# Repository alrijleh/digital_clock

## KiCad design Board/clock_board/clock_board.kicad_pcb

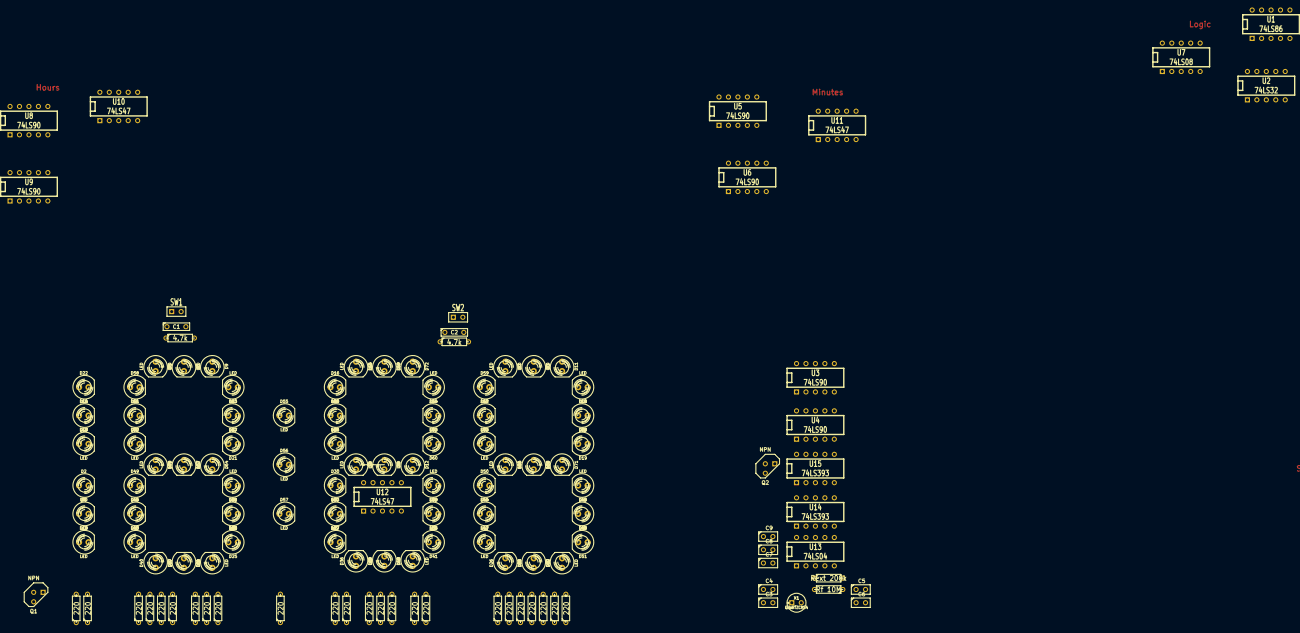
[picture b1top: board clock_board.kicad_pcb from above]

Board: 2 copper layers, 129 parts (0 on the bottom side), 74 nets, no tracks yet.

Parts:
C1, C2: .5uF; C2
C3: C1 15pF; C1
C4: C1 25pF; C1
C5: C2 25pF; C1
C6: C2 0pF; C1
C7, C8: Co 25pF; C1
C9: Co 0pF; C1
D1, D2, D3, D4, D5, D6, D7, D8, D9, D10, D11, D12, D13, D14, D15, D16, D17, D18, D19, D20, D21, D22, D23, D24, D25, D26, D27, D28, D29, D30, D31, D32, D33, D34, D35, D36, D37, D38, D39, D40, D41, D42, D43, D44, D45, D46, D47, D48, D49, D50, D51, D52, D53, D54, D55, D56, D57, D58, D59, D60, D61, D62, D63, D64, D65, D66, D67, D68, D69, D70, D71, D72: LED; LED-5MM
Q1, Q2: NPN; TO92
R1, R13: 4.7k; R3
R2, R3, R4, R5, R6, R7, R8, R9, R10, R11, R12, R14, R15, R16, R17, R18, R19, R20, R21, R22, R23, R24, R26, R27: 220; R3
R25: Rf 10M; R3
R28: Rext 200k; R3
SW1: min+; SIL-2
SW2: hour+; SIL-2
U1: 74LS86; DIP-10__300
U2: 74LS32; DIP-10__300
U3, U4, U5, U6, U8, U9: 74LS90; DIP-10__300
U7: 74LS08; DIP-10__300
U10, U11, U12: 74LS47; DIP-10__300
U13: 74LS04; DIP-10__300
U14, U15: 74LS393; DIP-10__300
X1: QUARTZCMS4; C1V5

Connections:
+5V: Q2.3, R2.1, R3.1, R4.1, R5.1, R6.1, R7.1, R8.1, R9.1, R10.1, R11.1, R12.1, R14.1, R15.1, R16.1, R17.1, R18.1, R19.1, R20.1, R21.1, R22.1, R23.1, R24.1, R26.1, R27.1
/hour H: Q1.2, U8.3
/hour+: C2.2, R13.2, SW2.2, U1.4
/min+: R1.2, U1.1, U2.1, U2.5, U3.2, U3.3
GND: C1.1, C2.1, C3.2, C4.2, C5.2, C6.2, C7.2, C8.2, C9.2, D55.2, D56.2, D57.2, Q1.1, R1.1, R13.1, U1.7, U2.7, U3.6, U3.7, U4.6, U4.7, U5.2, U5.3, U5.6, U5.7, U6.6, U6.7, U7.7, U8.6, U8.7, U9.6, U9.7, U10.8, U11.8, U12.8, U13.7, U14.2, U14.7, U15.2, U15.7
unnamed: U2.6, U4.2
unnamed: U2.3, U4.3
unnamed: U8.8, U10.2
unnamed: U1.2, U7.6
unnamed: U6.3, U6.8, U7.10, U12.2
unnamed: U6.2, U6.9, U7.9, U12.1
unnamed: U1.5, U7.8
unnamed: U5.9, U11.1
unnamed: U5.8, U11.2
unnamed: C3.1, C4.1, R25.2, U13.1, X1.1
unnamed: C5.1, C6.1, R25.1, R28.2
unnamed: U5.1, U11.7
unnamed: U6.1, U12.7
unnamed: U14.8, U15.1
unnamed: Q2.2, U15.9
unnamed: U7.2, U9.2, U10.7
unnamed: U7.1, U8.1, U8.9, U9.3, U10.1
unnamed: U7.3, U8.2
unnamed: D64.1, D67.1, D70.1, R24.2
unnamed: D2.1, D6.1, D10.1, R3.2
unnamed: D14.1, D18.1, D22.1, R7.2
unnamed: D55.1, D56.1, D57.1, R23.2
unnamed: C1.2, SW1.2
unnamed: D25.1, D28.1, D31.1, R10.2
unnamed: D34.1, D37.1, D40.1, R14.2
unnamed: D43.1, D46.1, D49.1, R17.2
unnamed: D52.1, D58.1, D61.1, R20.2
unnamed: C7.1, C8.1, C9.1, R28.1, U13.2, U14.1
unnamed: U2.4, U4.9, U7.4
unnamed: U2.2, U4.8, U7.5
unnamed: D53.1, D59.1, D62.1, R21.2
unnamed: D35.1, D38.1, D41.1, R15.2
unnamed: D44.1, D47.1, D50.1, R18.2
unnamed: D65.1, D68.1, D71.1, R26.2
unnamed: D4.1, D8.1, D12.1, R5.2
unnamed: D3.1, D7.1, D11.1, R4.2
unnamed: D15.1, D19.1, D23.1, R8.2
unnamed: D26.1, D29.1, D32.1, R11.2
unnamed: D54.1, D60.1, D63.1, R22.2
unnamed: D66.1, D69.1, D72.1, R27.2
unnamed: D1.1, D5.1, D9.1, R2.2
unnamed: D13.1, D17.1, D21.1, R6.2
unnamed: D16.1, D20.1, D24.1, R9.2
unnamed: D27.1, D30.1, D33.1, R12.2
unnamed: D36.1, D39.1, D42.1, R16.2
unnamed: D45.1, D48.1, D51.1, R19.2
unnamed: D15.2, D19.2, D23.2
unnamed: D26.2, D29.2, D32.2
unnamed: D3.2, D7.2, D11.2
unnamed: D4.2, D8.2, D12.2
unnamed: D65.2, D68.2, D71.2
unnamed: D16.2, D20.2, D24.2
unnamed: D35.2, D38.2, D41.2, U11.10
unnamed: D44.2, D47.2, D50.2, U11.9
unnamed: D53.2, D59.2, D62.2
unnamed: D2.2, D6.2, D10.2, D14.2, D18.2, D22.2, Q1.3
unnamed: D54.2, D60.2, D63.2
unnamed: D66.2, D69.2, D72.2
unnamed: D1.2, D5.2, D9.2
unnamed: D27.2, D30.2, D33.2, U12.9
unnamed: D36.2, D39.2, D42.2, U12.10
unnamed: D45.2, D48.2, D51.2
unnamed: D43.2, D46.2, D49.2, U10.9
unnamed: D52.2, D58.2, D61.2
unnamed: D64.2, D67.2, D70.2
unnamed: D13.2, D17.2, D21.2
unnamed: D25.2, D28.2, D31.2
unnamed: D34.2, D37.2, D40.2, U10.10
VCC: SW1.1, SW2.1, U3.5, U4.5, U5.5, U6.5, U8.5, U9.5, U10.3, U10.4, U10.5, U11.3, U11.4, U11.5, U12.3, U12.4, U12.5
